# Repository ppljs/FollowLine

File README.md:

# FollowLine

This is a simple project of a follow line robot, using IR leds and phototransistors. It's being done on EagleCad by myself and my friend Anderson Hiroshi.

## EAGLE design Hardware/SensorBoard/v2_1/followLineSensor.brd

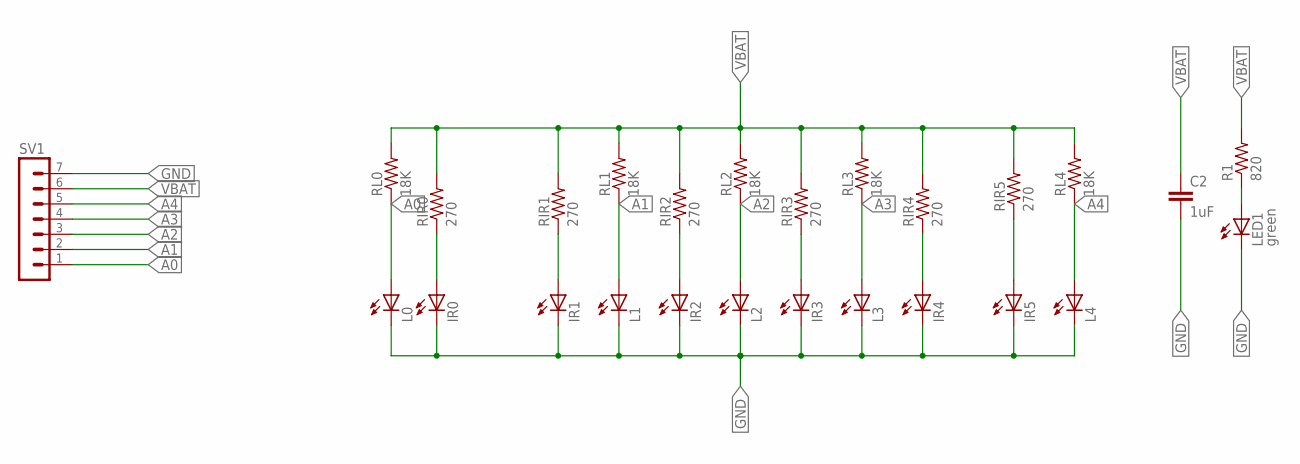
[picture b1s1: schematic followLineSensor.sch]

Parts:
C2: 1uF; C1206
IR0, IR1, IR2, IR3, IR4, IR5: LED5MM
L0, L1, L2, L3, L4: LED5MM
LED1: green; SML0805
R1: 820; R0805
RIR0, RIR1, RIR2, RIR3, RIR4, RIR5: 270; 1206
RL0, RL1, RL2, RL3, RL4: 18K; 1206
SV1: MA07-1

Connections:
A0: L0.A, RL0.1, SV1.1
A1: L1.A, RL1.1, SV1.2
A2: L2.A, RL2.1, SV1.3
A3: L3.A, RL3.1, SV1.4
A4: L4.A, RL4.1, SV1.5
GND: C2.2, IR0.K (C), IR1.K (C), IR2.K (C), IR3.K (C), IR4.K (C), IR5.K (C), L0.K (C), L1.K (C), L2.K (C), L3.K (C), L4.K (C), LED1.C, SV1.7
unnamed: IR1.A, RIR1.1
unnamed: LED1.A, R1.1
unnamed: IR5.A, RIR5.1
unnamed: IR4.A, RIR4.1
unnamed: IR3.A, RIR3.1
unnamed: IR2.A, RIR2.1
unnamed: IR0.A, RIR0.1
VBAT: C2.1, R1.2, RIR0.2, RIR1.2, RIR2.2, RIR3.2, RIR4.2, RIR5.2, RL0.2, RL1.2, RL2.2, RL3.2, RL4.2, SV1.6

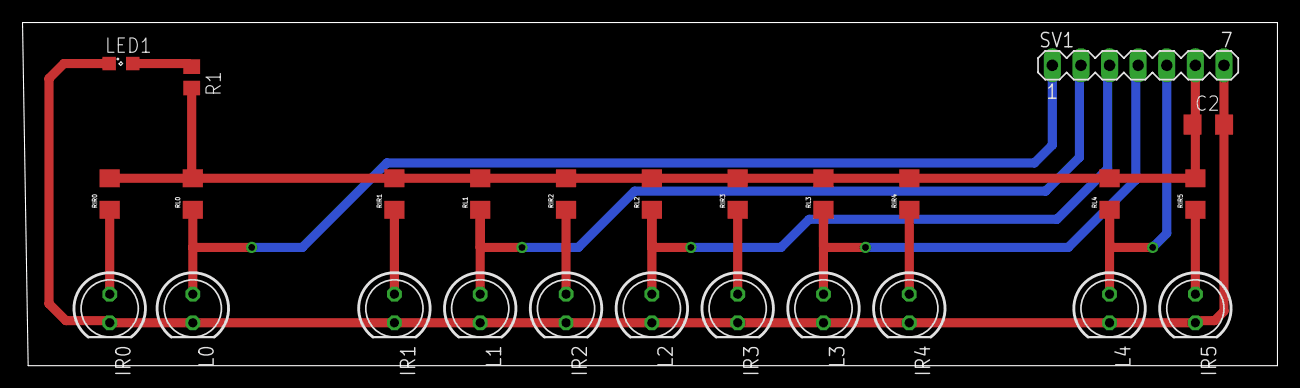
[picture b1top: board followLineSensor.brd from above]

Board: 2 copper layers, 111.4 x 30.5 mm, 26 parts (0 on the bottom side), 14 nets.

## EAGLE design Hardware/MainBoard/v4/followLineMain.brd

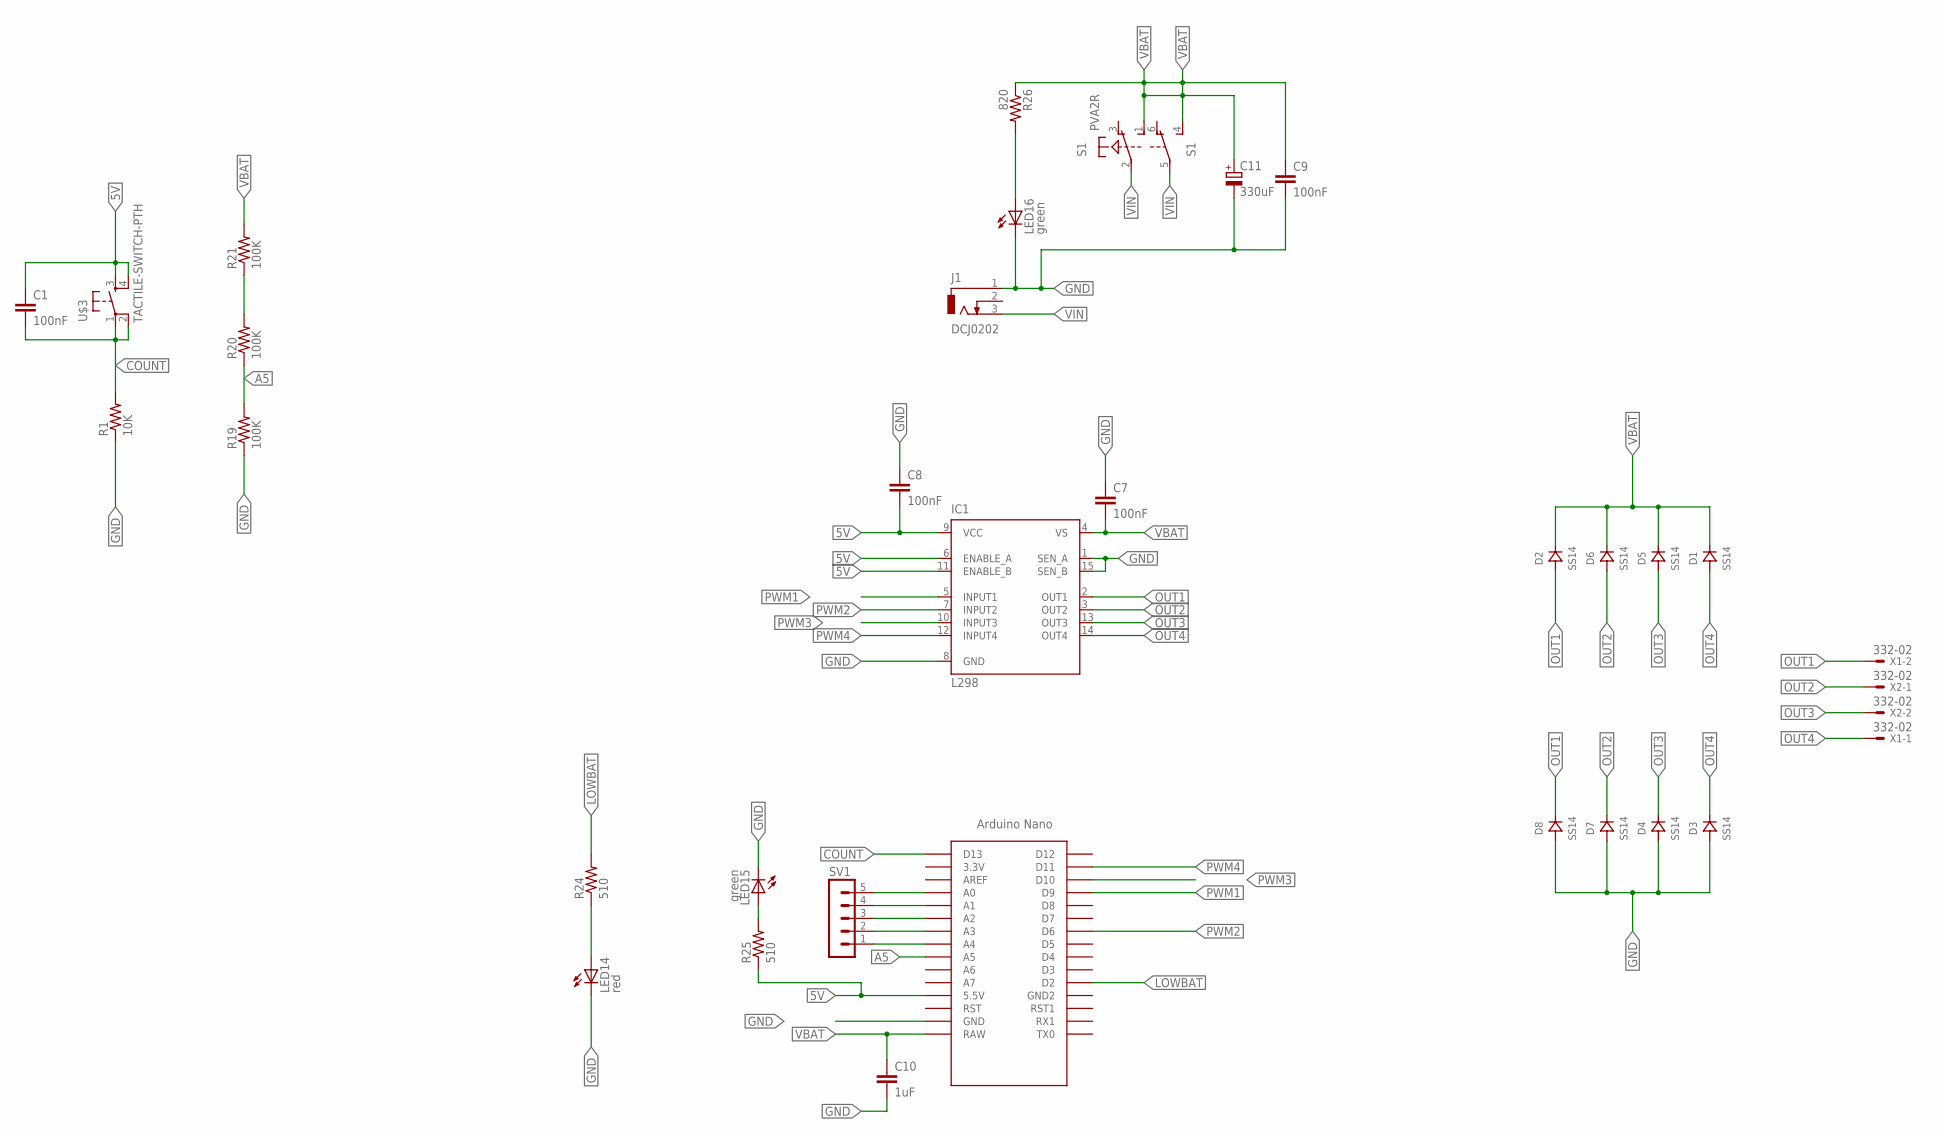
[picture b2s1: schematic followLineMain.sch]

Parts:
C1: 100nF; C0603
C7, C8, C9: 100nF; 0805
C10: 1uF; 1206
C11: 330uF; E5-13
D1, D2, D3, D4, D5, D6, D7, D8: SS14; DO214
IC1: L298; MULTIWATT-15
J1: DCJ0202
LED14: red; SML0805
LED15, LED16: green; SML0805
R1: 10K; 0805
R19, R20, R21: 100K; 0805
R24, R25: 510; 0805
R26: 820; 0805
S1: PVA2R
SV1: MA05-1
U$1: NANO
U$3: TACTILE-SWITCH-PTH; TAC-SWITCH-PTH
X1, X2: 332-02

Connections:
5V: C1.1, C8.2, IC1.6 (ENABLE_A), IC1.9 (VCC), IC1.11 (ENABLE_B), R25.1, U$1.5V (5.5V), U$3.3, U$3.4
A5: R19.2, R20.1, U$1.A5
COUNT: C1.2, R1.2, U$1.D13, U$3.1, U$3.2
GND: C7.1, C8.1, C9.2, C10.2, C11.-, D3.ANODE, D4.ANODE, D7.ANODE, D8.ANODE, IC1.1 (SEN_A), IC1.8 (GND), IC1.15 (SEN_B), J1.1, LED14.C, LED15.C, LED16.C, R1.1, R19.1, U$1.GND
LOWBAT: R24.2, U$1.D2
unnamed: LED16.A, R26.2
unnamed: LED14.A, R24.1
unnamed: SV1.1, U$1.A4
unnamed: SV1.2, U$1.A3
unnamed: R20.2, R21.1
unnamed: SV1.3, U$1.A2
unnamed: SV1.4, U$1.A1
unnamed: SV1.5, U$1.A0
unnamed: LED15.A, R25.2
OUT1: D2.ANODE, D8.CATHODE, IC1.2 (OUT1), X1.2
OUT2: D6.ANODE, D7.CATHODE, IC1.3 (OUT2), X2.1
OUT3: D4.CATHODE, D5.ANODE, IC1.13 (OUT3), X2.2
OUT4: D1.ANODE, D3.CATHODE, IC1.14 (OUT4), X1.1
PWM1: IC1.5 (INPUT1), U$1.D9
PWM2: IC1.7 (INPUT2), U$1.D6
PWM3: IC1.10 (INPUT3), U$1.D10
PWM4: IC1.12 (INPUT4), U$1.D11
VBAT: C7.2, C9.1, C10.1, C11.+, D1.CATHODE, D2.CATHODE, D5.CATHODE, D6.CATHODE, IC1.4 (VS), R21.2, R26.1, S1.1 (S), S1.4 (S), U$1.RAW
VIN: J1.3, S1.2, S1.5

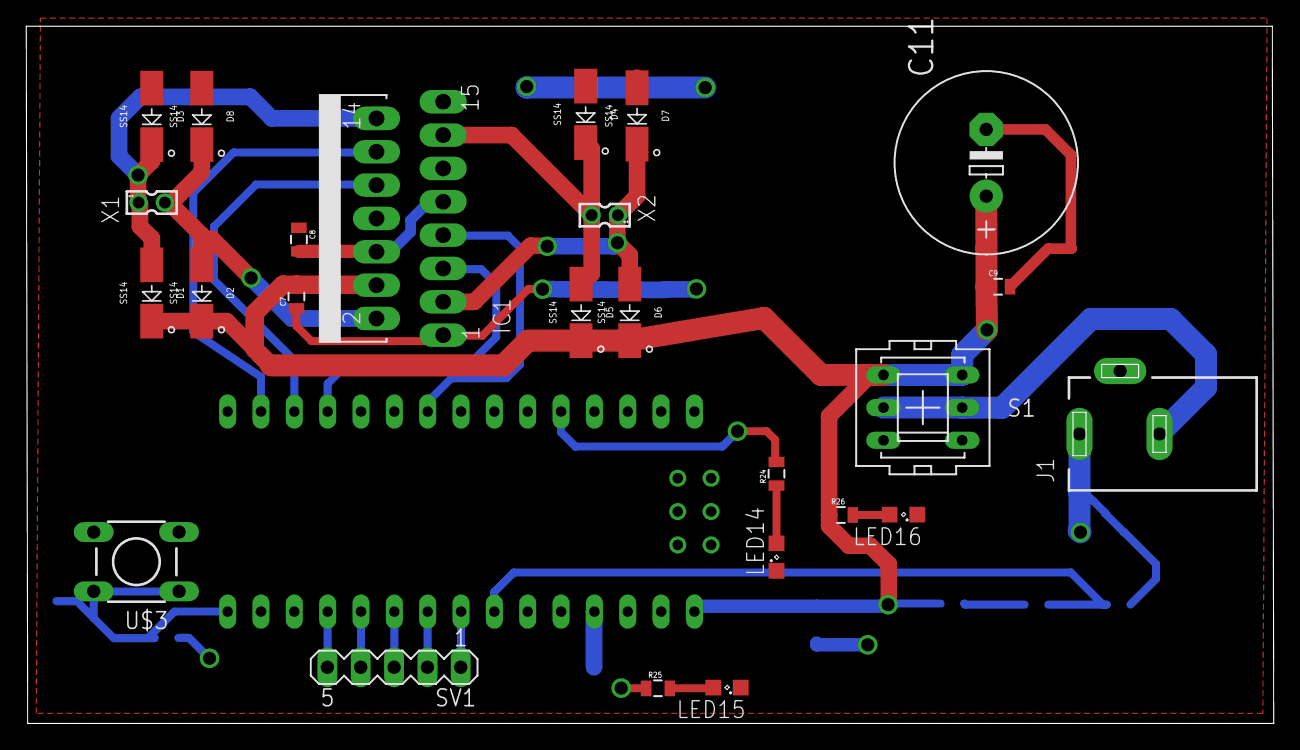
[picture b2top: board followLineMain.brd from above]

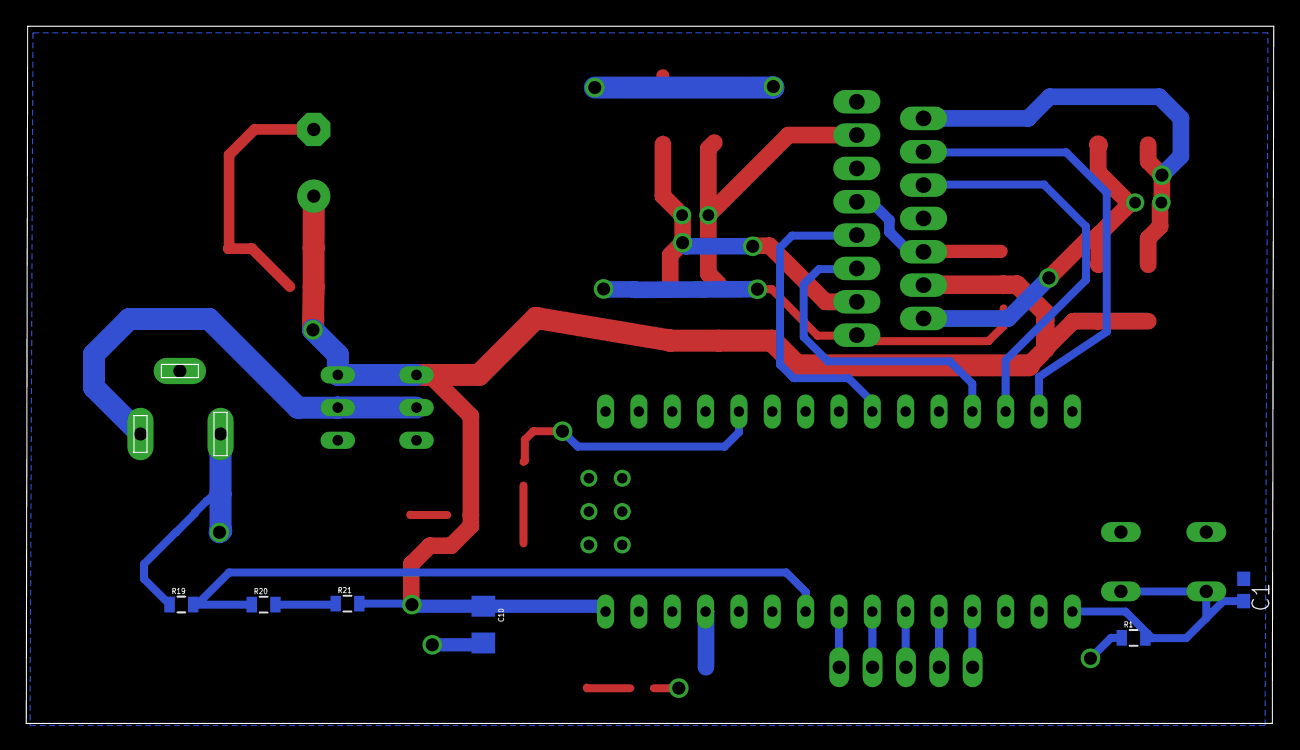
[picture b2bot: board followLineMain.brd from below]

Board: 2 copper layers, 95.0 x 53.1 mm, 32 parts (6 on the bottom side), 24 nets.

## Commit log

2016-10-21 The first, unverified version of FollowLine proj
2016-10-21 Edited the readme
2016-10-21 Added a second version for the MainBoard layout
2016-10-21 Corrected some aspects of the boards and another version of the SensorBoard
2016-10-24 Another better versions of the boards done
2016-10-24 Improved the ground trace to the H-bridge
2016-10-27 Minor changes on brd main file
2016-11-12 Added another folder with our thoughts
2016-12-13 nothing changed...
2016-12-14 Separeted the Follow line project in two folders, and started the creation of the robots firmware
2016-12-15 Sensor Board version 2.1
2016-12-15 rename SensorBoard v2.1 to SensorBoard v3
2016-12-15 Minor changes in SensorBoard v3
2016-12-15 Added copper pours to SensorBoard
2016-12-16 Added the arduino code for the follow-line robot, the code is not half complete
2017-05-22 Change led position

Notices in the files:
parts and their libraries:
SparkFun-Capacitors: Licensing: Creative Commons ShareAlike 4.0 International - https://creativecommons.org/licenses/by-sa/4.0
